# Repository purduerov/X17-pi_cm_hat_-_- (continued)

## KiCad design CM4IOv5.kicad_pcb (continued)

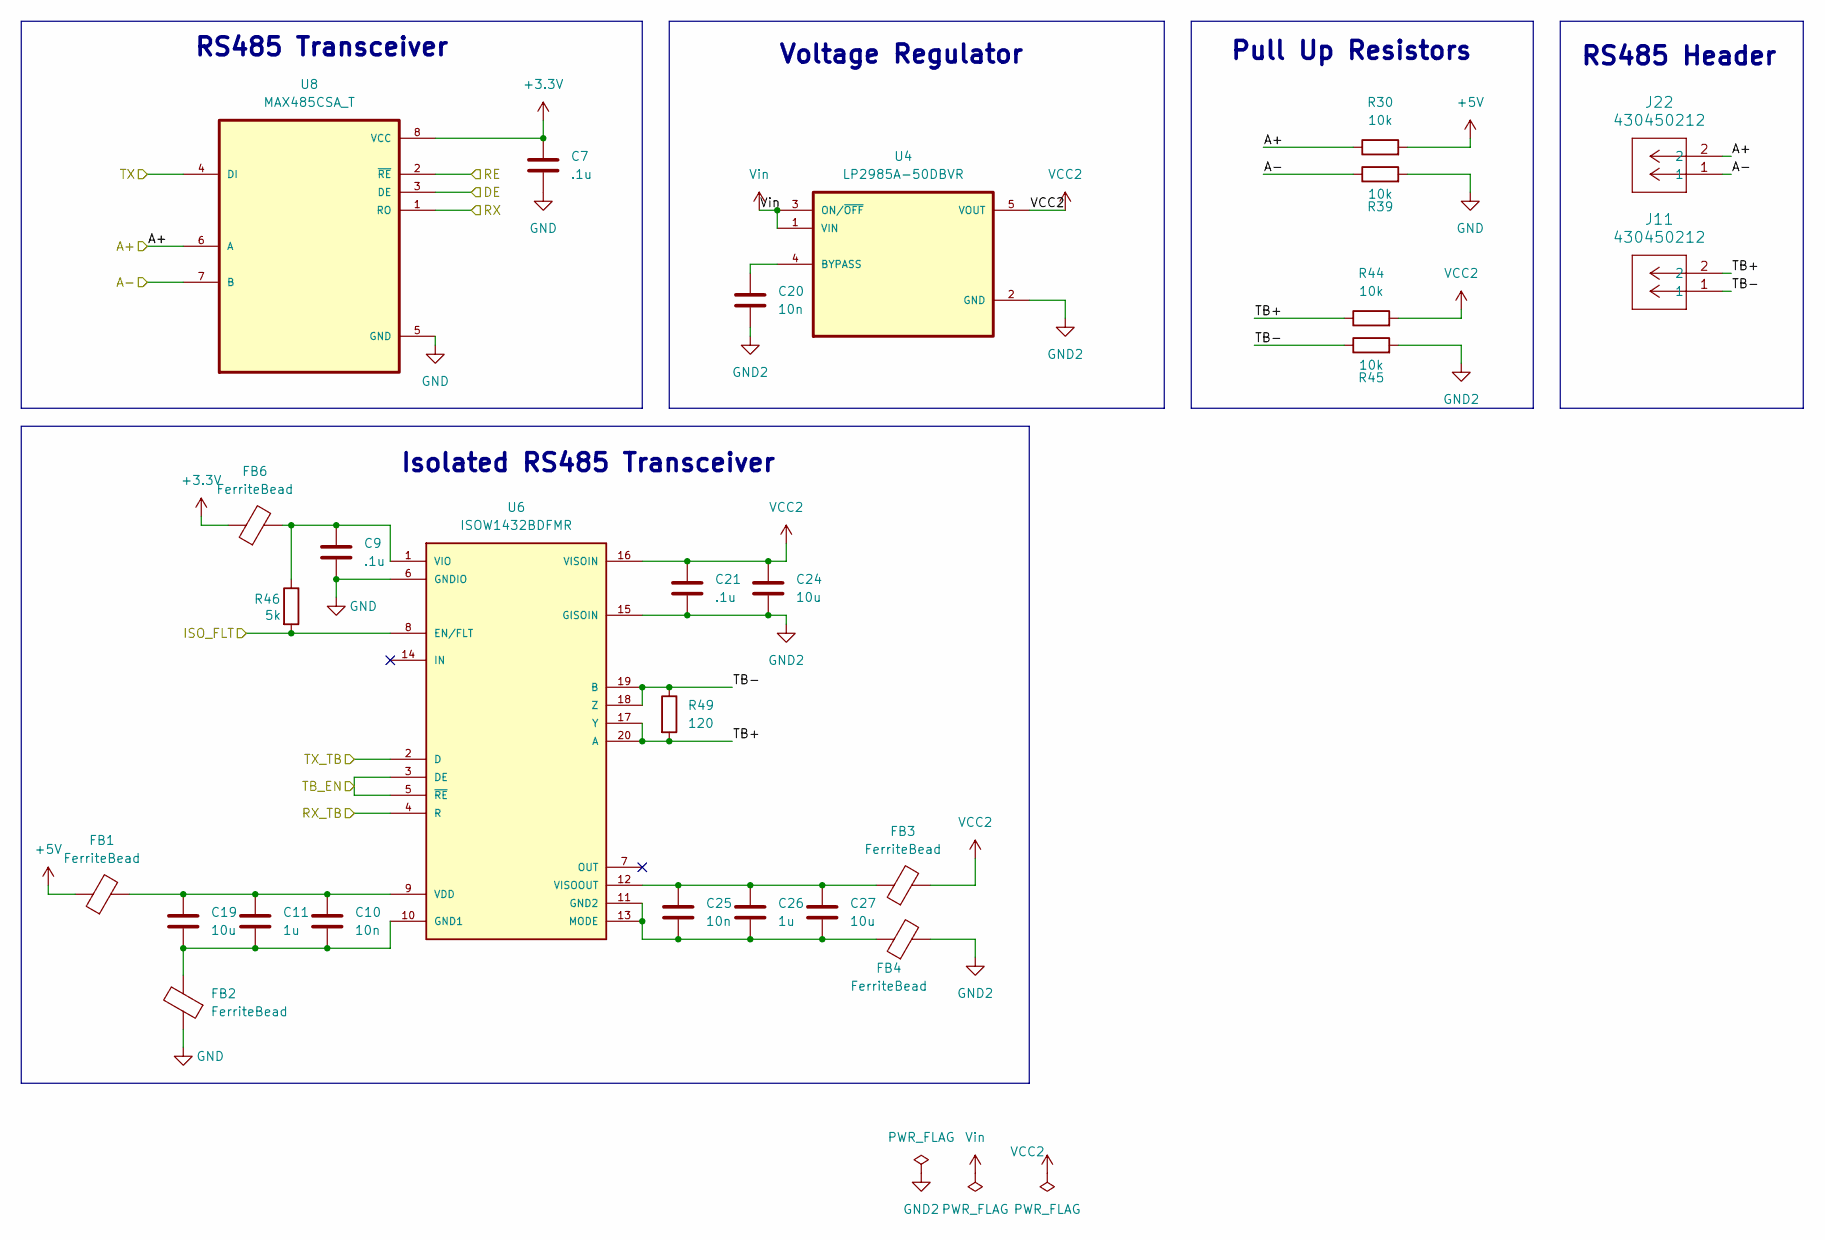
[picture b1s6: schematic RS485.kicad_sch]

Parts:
C7, C9, C21: .1u; C_0805_2012Metric
C10, C20, C25: 10n; C_0805_2012Metric
C11, C26: 1u; C_0805_2012Metric
C19, C24, C27: 10u; C_0805_2012Metric
FB1, FB2, FB3, FB4, FB6: FerriteBead; L_Bourns_SRN6045TA
J11, J22: 430450212; CON_430450212_MOL
R30, R39, R44, R45: 10k; R_0805_2012Metric
R46: 5k; R_0805_2012Metric
R49: 120; R_0805_2012Metric
U4: LP2985A-50DBVR; SOT95P280X145-5N
U6: ISOW1432BDFMR; SOIC127P1030X355-20N; PARTREV B
U8: MAX485CSA_T; SOIC127P600X175-8N

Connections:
+3.3V: C7.1, FB6.1, U8.8 (VCC); also elsewhere on the board
+5V: FB1.1, R30.2; also elsewhere on the board
/A+: J22.2, R30.1, U8.6 (A); also elsewhere on the board
/A-: J22.1, R39.1, U8.7 (B); also elsewhere on the board
/CM4_GPIO ( Ethernet, GPIO, SDCARD)/RX_TB: U6.4 (R); also elsewhere on the board
/CM4_GPIO ( Ethernet, GPIO, SDCARD)/TB_EN: U6.3 (DE), U6.5 (~RE); also elsewhere on the board
/CM4_GPIO ( Ethernet, GPIO, SDCARD)/TX_TB: U6.2 (D); also elsewhere on the board
/DE: U8.3 (DE); also elsewhere on the board
/ISO_FLT: R46.2, U6.8 (EN/FLT); also elsewhere on the board
/RE: U8.2 (~RE); also elsewhere on the board
/RS485/TB+: J11.2, R44.1, R49.2, U6.17 (Y), U6.20 (A)
/RS485/TB-: J11.1, R45.1, R49.1, U6.18 (Z), U6.19 (B)
/RX: U8.1 (RO); also elsewhere on the board
/TX: U8.4 (DI); also elsewhere on the board
GND: C7.2, C9.2, FB2.1, R39.2, U6.6 (GNDIO), U8.5 (GND); also elsewhere on the board
GND2: C20.2, C21.2, C24.2, FB4.2, R45.2, U4.2 (GND), U6.15 (GISOIN)
unnamed: C20.1, U4.4 (BYPASS)
unnamed: C10.2, C11.2, C19.2, FB2.2, U6.10 (GND1)
unnamed: C25.2, C26.2, C27.2, FB4.1, U6.11 (GND2), U6.13 (MODE)
unnamed: C10.1, C11.1, C19.1, FB1.2, U6.9 (VDD)
unnamed: C9.1, FB6.2, R46.1, U6.1 (VIO)
unnamed: C25.1, C26.1, C27.1, FB3.1, U6.12 (VISOOUT)
VCC2: C21.1, C24.1, FB3.2, R44.2, U4.5 (VOUT), U6.16 (VISOIN)
Vin: U4.1 (VIN), U4.3 (ON/~OFF)

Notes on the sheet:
RS485 Header
Pull Up Resistors
RS485 Transceiver
Voltage Regulator
Isolated RS485 Transceiver

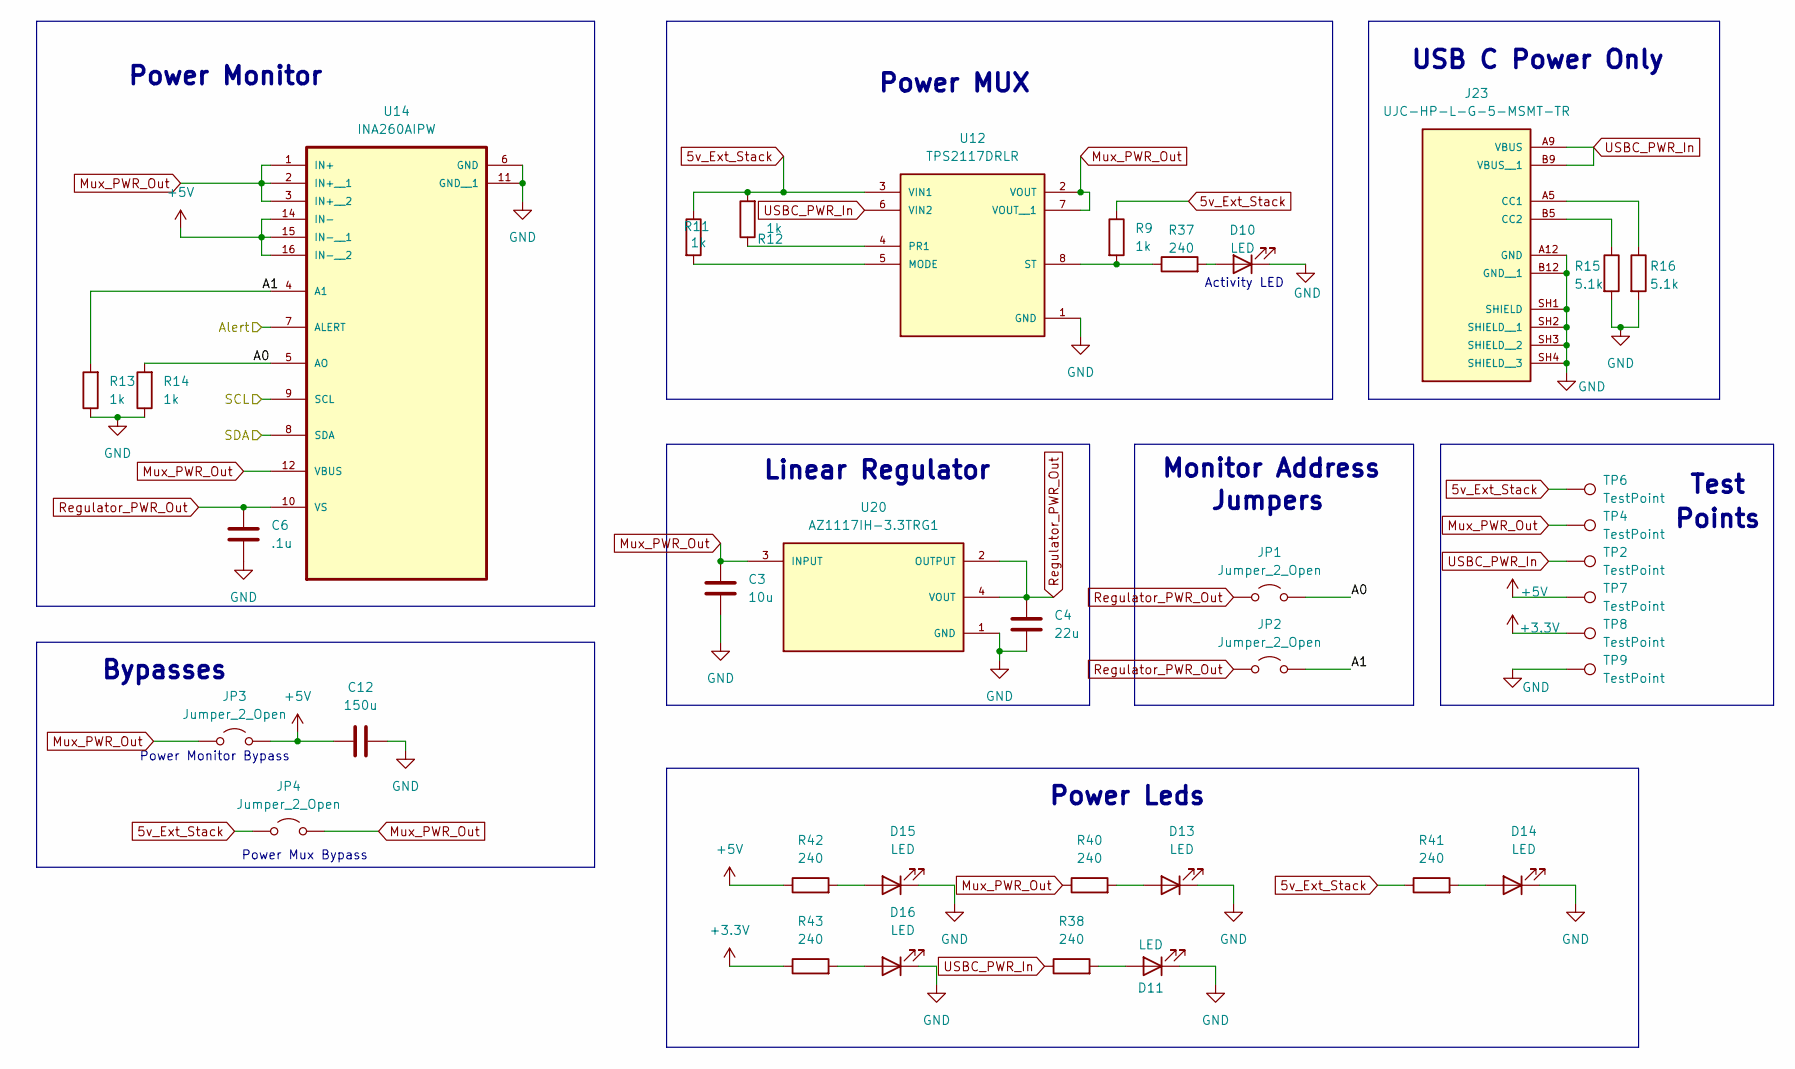
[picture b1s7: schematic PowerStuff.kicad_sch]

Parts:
C3: 10u; C_0805_2012Metric
C4: 22u; C_0805_2012Metric
C6: .1u; C_0805_2012Metric
C12: 150u; C_0805_2012Metric
D10, D11, D13, D14, D15, D16: LED; LED_0805_2012Metric
J23: UJC-HP-L-G-5-MSMT-TR; CUI_UJC-HP-L-G-5-MSMT-TR; PARTREV 1.01
JP1, JP2, JP3, JP4: Jumper_2_Open; SolderJumper-2_P1.3mm_Open_RoundedPad1.0x1.5mm
R9, R11, R12, R13, R14: 1k; R_0805_2012Metric
R15, R16: 5.1k; R_0805_2012Metric
R37, R38, R40, R41, R42, R43: 240; R_0805_2012Metric
TP2, TP4, TP6, TP7, TP8, TP9: TestPoint; TestPoint_Plated_Hole_D3.0mm
U12: TPS2117DRLR; SOTFL50P160X60-8N; PARTREV A
U14: INA260AIPW; SOP65P640X120-16N
U20: AZ1117IH-3.3TRG1; SOT230P700X185-4N; PARTREV 2-2

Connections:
5v_Ext_Stack: JP4.1 (A), R9.1, R11.1, R12.2, R41.1, TP6.1, U12.3 (VIN1); also elsewhere on the board
+3.3V: R43.1, TP8.1; also elsewhere on the board
+5V: C12.1, JP3.2 (B), R42.1, TP7.1, U14.14 (IN-), U14.15 (IN-__1), U14.16 (IN-__2); also elsewhere on the board
/Alert: U14.7 (ALERT); also elsewhere on the board
/Power Stuff/A0: JP1.2 (B), R14.2, U14.5 (AO)
/Power Stuff/A1: JP2.2 (B), R13.2, U14.4 (A1)
/SCL: U14.9 (SCL); also elsewhere on the board
/SDA: U14.8 (SDA); also elsewhere on the board
GND: C3.2, C4.2, C6.2, C12.2, D10.1 (K), D11.1 (K), D13.1 (K), D14.1 (K), D15.1 (K), D16.1 (K), J23.A12 (GND), J23.B12 (GND__1), J23.SH1 (SHIELD), J23.SH2 (SHIELD__1), J23.SH3 (SHIELD__2), J23.SH4 (SHIELD__3), R13.1, R14.1, R15.2, R16.2, TP9.1, U12.1 (GND), U14.6 (GND), U14.11 (GND__1), U20.1 (GND); also elsewhere on the board
Mux_PWR_Out: C3.1, JP3.1 (A), JP4.2 (B), R40.1, TP4.1, U12.2 (VOUT), U12.7 (VOUT__1), U14.1 (IN+), U14.2 (IN+__1), U14.3 (IN+__2), U14.12 (VBUS), U20.3 (INPUT)
unnamed: D10.2 (A), R37.2
unnamed: D11.2 (A), R38.2
unnamed: D13.2 (A), R40.2
unnamed: D14.2 (A), R41.2
unnamed: D15.2 (A), R42.2
unnamed: D16.2 (A), R43.2
unnamed: J23.A5 (CC1), R16.1
unnamed: J23.B5 (CC2), R15.1
unnamed: R11.2, U12.5 (MODE)
unnamed: R12.1, U12.4 (PR1)
unnamed: R9.2, R37.1, U12.8 (ST)
Regulator_PWR_Out: C4.1, C6.1, JP1.1 (A), JP2.1 (A), U14.10 (VS), U20.2 (OUTPUT), U20.4 (VOUT)
USBC_PWR_In: J23.A9 (VBUS), J23.B9 (VBUS__1), R38.1, TP2.1, U12.6 (VIN2)

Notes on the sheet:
Points
Activity LED
Power Mux Bypass
Power Monitor Bypass
Linear Regulator
Jumpers
USB C Power Only
Power Leds
Test
Monitor Address
Bypasses
Power MUX
Power Monitor

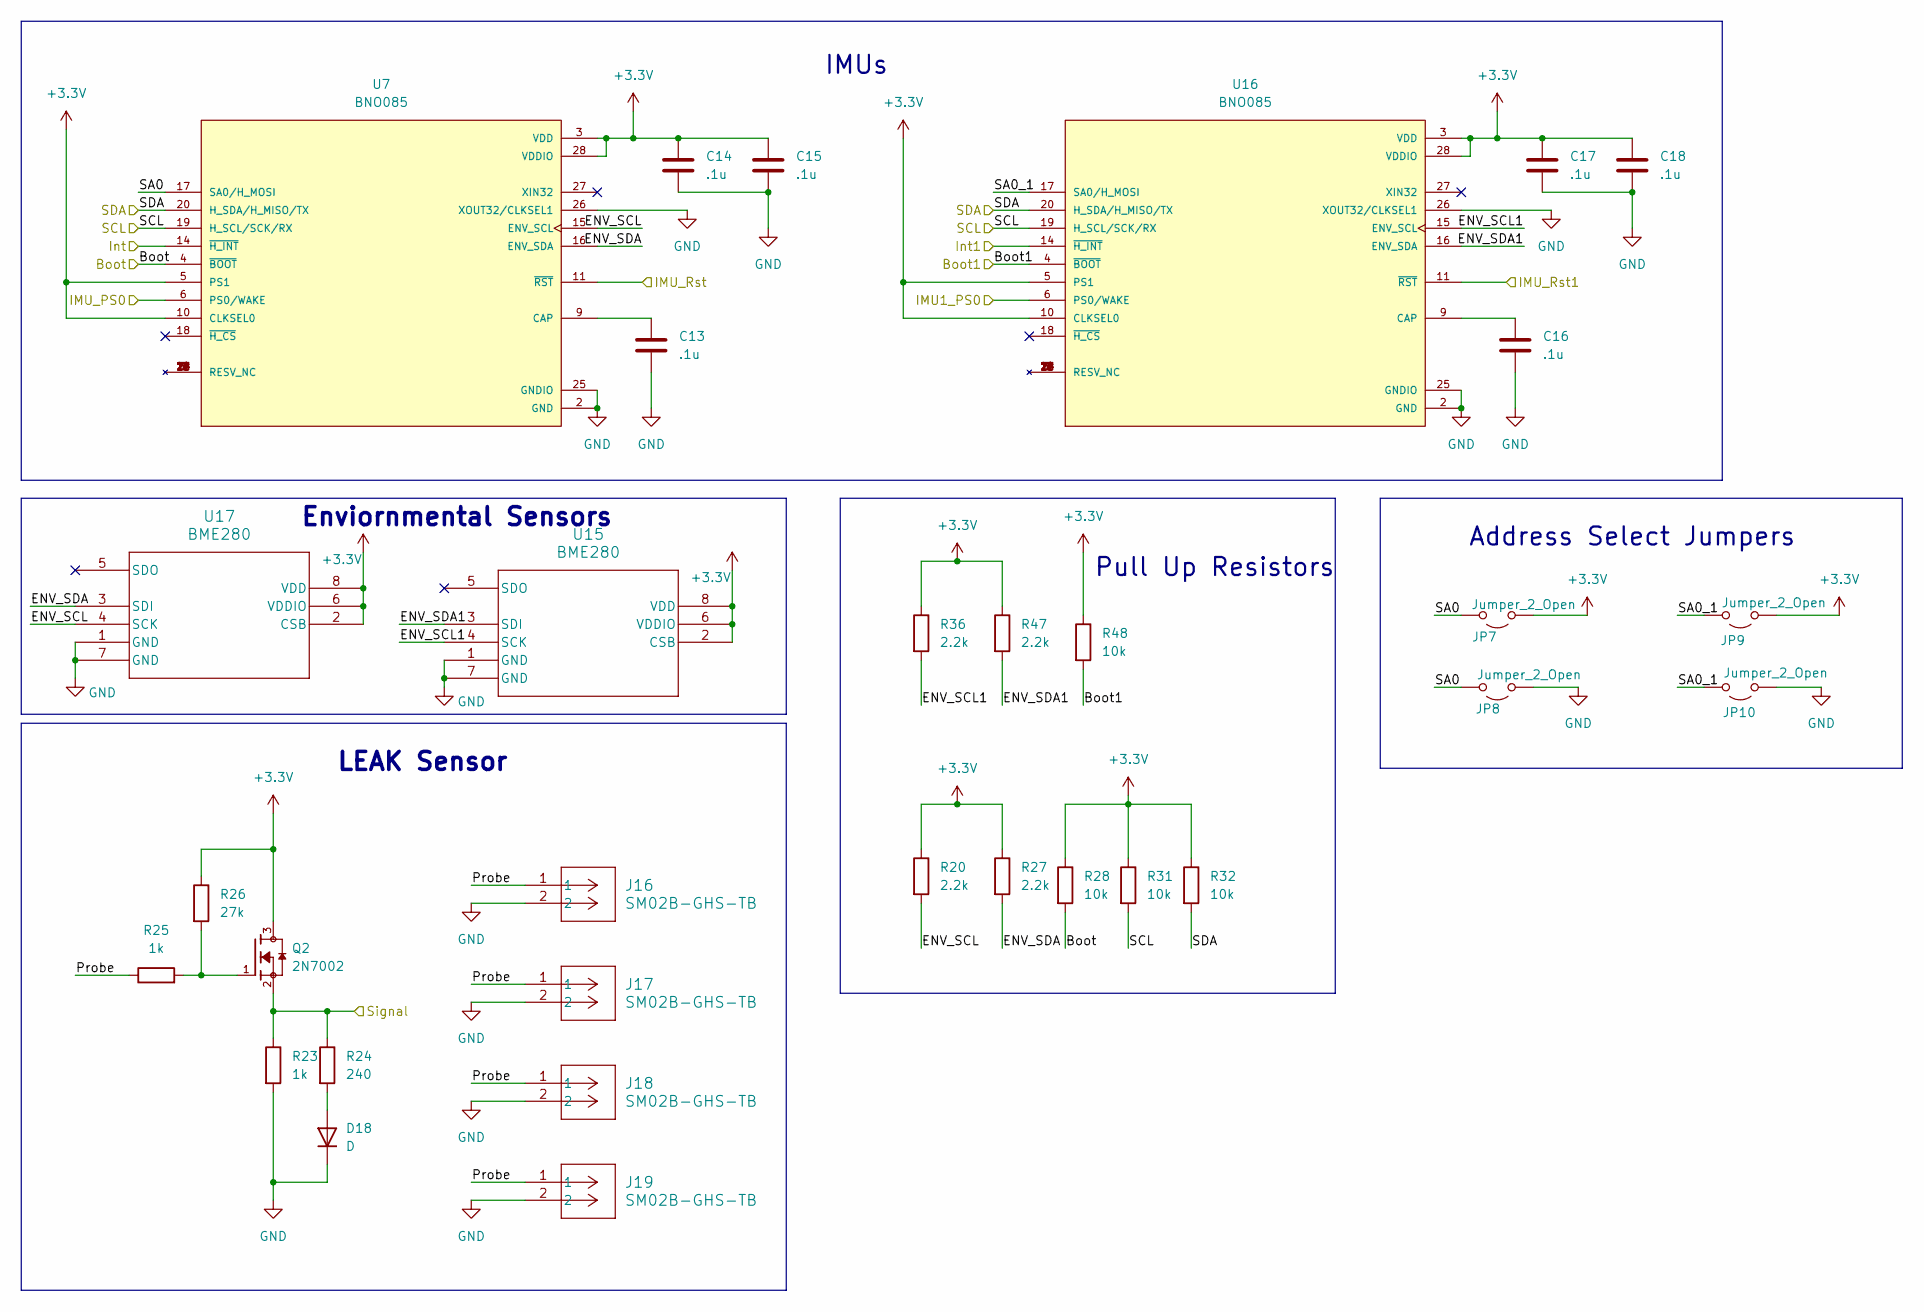
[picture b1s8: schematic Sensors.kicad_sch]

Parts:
C13, C14, C15, C16, C17, C18: .1u; C_0805_2012Metric
D18: D; LED_0805_2012Metric
J16, J17, J18, J19: SM02B-GHS-TB; CONN_SM02B-GHS_JST
JP7, JP8, JP9, JP10: Jumper_2_Open; SolderJumper-2_P1.3mm_Open_RoundedPad1.0x1.5mm
Q2: 2N7002; TRANS_2N7002; PARTREV 2023-01-11
R20, R27, R36, R47: 2.2k; R_0805_2012Metric
R23, R25: 1k; R_0805_2012Metric
R24: 240; R_0805_2012Metric
R26: 27k; R_0805_2012Metric
R28, R31, R32, R48: 10k; R_0805_2012Metric
U7, U16: BNO085; SQFN36_M2_MCH; PARTREV v1.17
U15, U17: BME280; DFN8_0p65_2p5SQ_BOS

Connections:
+3.3V: C14.1, C15.1, C17.1, C18.1, JP7.1 (A), JP9.1 (A), Q2.3, R20.1, R26.1, R27.1, R28.1, R31.1, R32.1, R36.1, R47.1, R48.1, U7.3 (VDD), U7.5 (PS1), U7.10 (CLKSEL0), U7.28 (VDDIO), U15.2 (CSB), U15.6 (VDDIO), U15.8 (VDD), U16.3 (VDD), U16.5 (PS1), U16.10 (CLKSEL0), U16.28 (VDDIO), U17.2 (CSB), U17.6 (VDDIO), U17.8 (VDD); also elsewhere on the board
/Boot: R28.2, U7.4 (~BOOT); also elsewhere on the board
/CM4_GPIO ( Ethernet, GPIO, SDCARD)/Boot1: R48.2, U16.4 (~BOOT); also elsewhere on the board
/CM4_GPIO ( Ethernet, GPIO, SDCARD)/IMU1_PS0: U16.6 (PS0/WAKE); also elsewhere on the board
/CM4_GPIO ( Ethernet, GPIO, SDCARD)/IMU_PS0: U7.6 (PS0/WAKE); also elsewhere on the board
/CM4_GPIO ( Ethernet, GPIO, SDCARD)/IMU_Rst1: U16.11 (~RST); also elsewhere on the board
/CM4_GPIO ( Ethernet, GPIO, SDCARD)/Int1: U16.14 (~H_INT); also elsewhere on the board
/IMU_Rst: U7.11 (~RST); also elsewhere on the board
/Int: U7.14 (~H_INT); also elsewhere on the board
/Leak: Q2.2, R23.1, R24.1; also elsewhere on the board
/SCL: R31.2, U7.19 (H_SCL/SCK/RX), U16.19 (H_SCL/SCK/RX); also elsewhere on the board
/SDA: R32.2, U7.20 (H_SDA/H_MISO/TX), U16.20 (H_SDA/H_MISO/TX); also elsewhere on the board
/Sensors/ENV_SCL: R20.2, U7.15 (ENV_SCL), U17.4 (SCK)
/Sensors/ENV_SCL1: R36.2, U15.4 (SCK), U16.15 (ENV_SCL)
/Sensors/ENV_SDA: R27.2, U7.16 (ENV_SDA), U17.3 (SDI)
/Sensors/ENV_SDA1: R47.2, U15.3 (SDI), U16.16 (ENV_SDA)
/Sensors/Probe: J16.1, J17.1, J18.1, J19.1, R25.1
/Sensors/SA0: JP7.2 (B), JP8.2 (B), U7.17 (SA0/H_MOSI)
/Sensors/SA0_1: JP9.2 (B), JP10.2 (B), U16.17 (SA0/H_MOSI)
GND: C13.2, C14.2, C15.2, C16.2, C17.2, C18.2, D18.1 (K), J16.2, J17.2, J18.2, J19.2, JP8.1 (A), JP10.1 (A), R23.2, U7.2 (GND), U7.25 (GNDIO), U7.26 (XOUT32/CLKSEL1), U15.1 (GND), U15.7 (GND), U16.2 (GND), U16.25 (GNDIO), U16.26 (XOUT32/CLKSEL1), U17.1 (GND), U17.7 (GND); also elsewhere on the board
unnamed: D18.2 (A), R24.2
unnamed: Q2.1, R25.2, R26.2
unnamed: C13.1, U7.9 (CAP)
unnamed: C16.1, U16.9 (CAP)

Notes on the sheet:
IMUs
Address Select Jumpers
Pull Up Resistors
LEAK Sensor
Enviornmental Sensors

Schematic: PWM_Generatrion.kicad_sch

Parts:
J14, J20: DF11-10DP-2DSA24; CON10_2X5_UF_DF11_HIR
U22: PCA9685PW_118; SOP65P640X110-28N; MPN PCA9685PW,118

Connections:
+3.3V: U22.28 (VDD); also elsewhere on the board
/OE_PWM: U22.23 (~OE); also elsewhere on the board
/PWM_Generatrion/0: J14.6, U22.6 (LED0)
/PWM_Generatrion/1: J14.5, U22.7 (LED1)
/PWM_Generatrion/2: J14.8, U22.8 (LED2)
/PWM_Generatrion/3: J14.7, U22.9 (LED3)
/PWM_Generatrion/4: J14.10, U22.10 (LED4)
/PWM_Generatrion/5: J14.9, U22.11 (LED5)
/PWM_Generatrion/6: J20.2, U22.12 (LED6)
/PWM_Generatrion/7: J20.1, U22.13 (LED7)
/PWM_Generatrion/8: J20.4, U22.15 (LED8)
/PWM_Generatrion/9: J20.3, U22.16 (LED9)
/SCL: U22.26 (SCL); also elsewhere on the board
/SDA: U22.27 (SDA); also elsewhere on the board
GND: U22.1 (A0), U22.2 (A1), U22.3 (A2), U22.4 (A3), U22.5 (A4), U22.14 (VSS), U22.24 (A5); also elsewhere on the board

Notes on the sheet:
ESC Controller Connector
PWM Generator

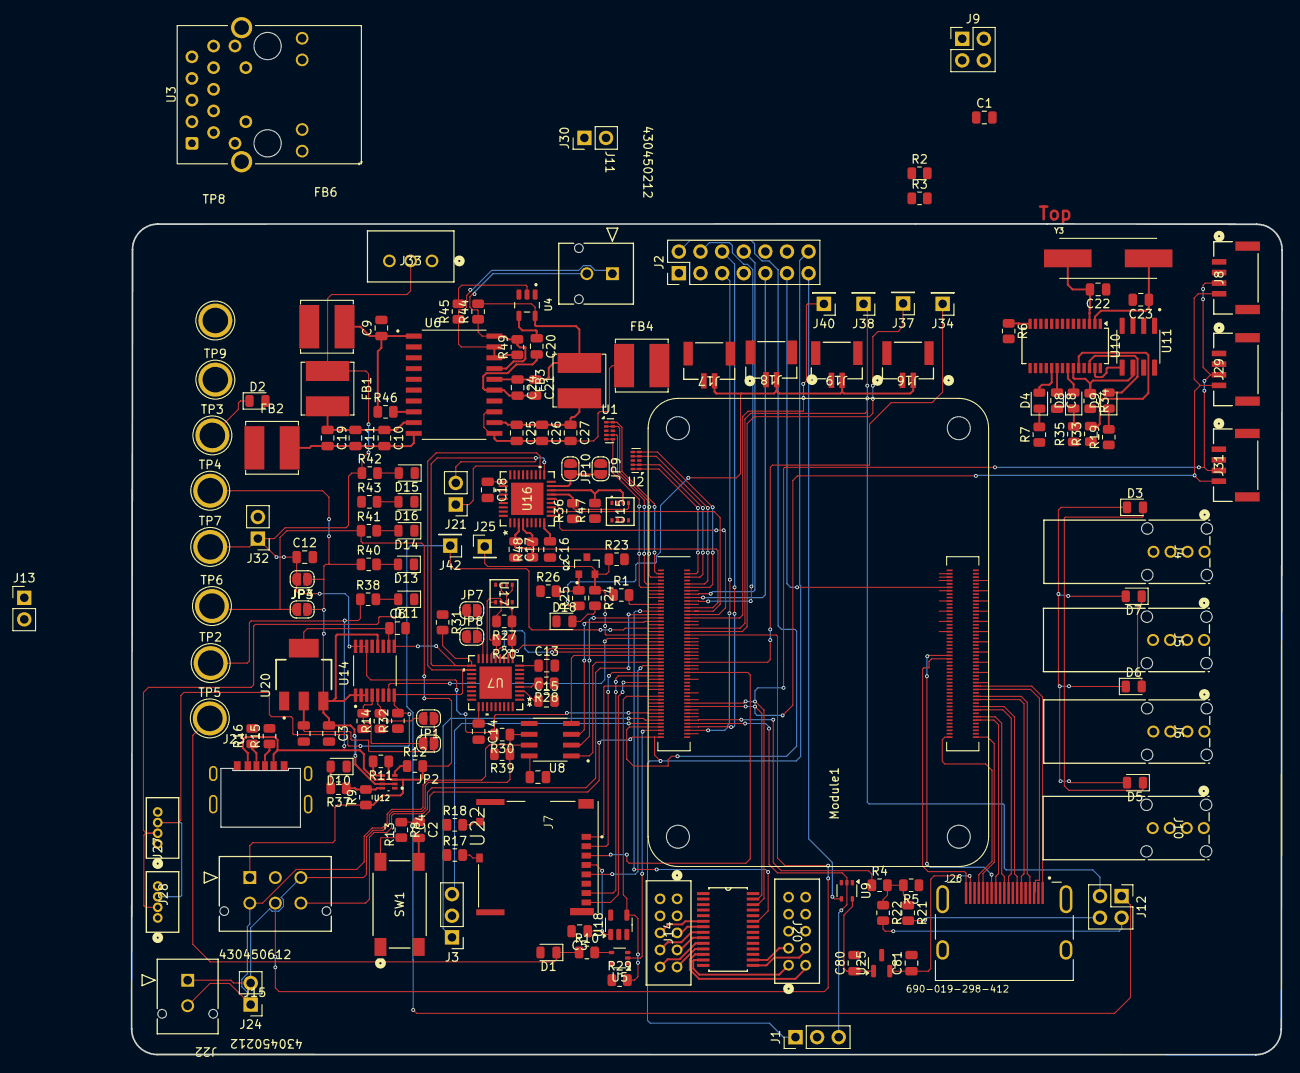
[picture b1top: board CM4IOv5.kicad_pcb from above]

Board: 4 copper layers, 135.2 x 97.6 mm, 185 parts (0 on the bottom side), 171 nets.

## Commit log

2024-10-09 board
2024-10-10 changes stuff
2024-10-10 stuff
2024-11-01 minor erc fixes
2024-11-05 assigned footprints
